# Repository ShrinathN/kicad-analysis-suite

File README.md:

# kicad-analysis-suite

**PCB Analysis Suite for KiCad**: a KiCad 10 plugin, also usable standalone, for analysing printed circuit boards. It has five tools so far:

- **DC & Thermal**: current density, IR drop and temperature on a real board, including resistance elements, linear and switching regulators (with their losses and junction temperature), current pulses (fusing) and magnetic field maps.
- **Switching Loop**: the hot loop and gate loops of a switching power stage (buck, boost, half-bridge, 4-switch buck-boost; synchronous or with a diode): loop inductance and where it sits, ringing frequency, gate-loop and common-source inductance, from a partial-inductance (PEEC) solve of the layout; switching edges in time, a snubber designer and an EMI estimate.
- **PDN (AC)**: the impedance of a supply rail seen by each chip, from the board's copper, the decoupling capacitors and the regulator, against the target impedance; which capacitors matter, plane resonances, and the rail's voltage over time when the loads step, with the regulator's control loop fitted to its datasheet's load-transient plot.
- **Trace R/L/C → SPICE**: R, L, C, Z₀ and delay of the copper between any pads, from a 2D field solve of each cross-section, exported as a SPICE RLC subcircuit.
- **Matching & Tolerance**: draw an RF matching network with real parts, then see whether it still meets its specs across part tolerances.

**Simulation tests**: keep any tool's setup as a test with pass / fail checks (T_max < 85 °C, the rail within its target, loop L < 3 nH, …) and rerun them whenever the board changes, from the command line, a Makefile or a script. Each run writes a report to `simulations/<timestamp>/` and compares it with the previous run:

```sh
python3 -m pcb_current_sim init board.kicad_pcb                       # tests from the setups you made in the windows
python3 -m pcb_current_sim run board.simtests.toml --test "3V3 rail"   # or --all; exit code 1 when a check fails
```

More tools (3D extraction, full-wave export, signal integrity) are planned. See the [roadmap](docs/ROADMAP.md).

## DC & Thermal

Pick the pads where current enters and leaves, or add voltage sources and loads, and solve all of them together on the board's copper.

| Current density | Temperature (electro-thermal) |
|---|---|
|  |  |
| **Magnetic field above the board** | **3D view** |
|  |  |

- Reads tracks, arcs, vias, filled zones, pads and the stackup directly from the `.kicad_pcb` file.
- Current paths, loads and voltage sources. Resistors on the board are found automatically, and any two pads can be joined by a resistance (FET R_on, inductor DCR, external load).
- Electro-thermal coupling with temperature-dependent copper resistance and natural convection plus radiation.
- Pulse heating and fusing, magnetic field maps and loop inductance.
- Tables per pad, via, track and element; export to PDF, HTML, CSV, PNG/SVG and ParaView.

## Switching Loop

Pick the switch node (or let the tool find it): it finds the switching parts, the hot-loop capacitors and the gate drives (driver pin, gate resistor, gate, return pin) and meshes the copper of all their nets, ground included, as conductors. A partial-inductance (PEEC) solve gives the copper's impedance between the parts' pins; the parts add their datasheet models (package inductance, capacitances, ESL).

- For each switching edge: the loop inductance across the switch that turns off, split into board copper and parts, and a bar chart of where it sits (each net and layer, vias, each package, each capacitor's ESL).
- The ringing frequency and Q with the switch's own capacitance, the expected overshoot per A/ns, and a starting snubber.
- Per FET: the gate-loop inductance, gate ringing, and the common-source inductance (the mutual between the gate loop and the power loop), which slows switching.
- Current-density and inductance-density maps at the ringing frequency, board capacitance between the nets, and a SPICE subcircuit of the copper (coupled inductors).

- **Switching edges** (simulated in time): one turn-on and one turn-off of the hard-switched switch at the inductor current you give, with the copper and the parts as one circuit: switch-node overshoot and ringing, dv/dt, di/dt, switching loss (E_on + E_off) × f_sw, reverse recovery, and how far the other FET's gate is pushed toward its threshold (shoot-through risk). A built-in solver uses the datasheet values; a FET can instead use its manufacturer's SPICE model, simulated in ngspice (bundled with KiCad).
- A cell diagram, readiness checks with one-click fixes, and a plain-language "What it means" summary.

| | |
|---|---|
|  |  |
|  |  |

## PDN (AC)

Pick a rail and its return nets: the tool finds the decoupling capacitors, the regulator and the chips on the rail, meshes the rail's copper over its return planes, and sweeps the impedance at every chip from 10 Hz to the GHz range.

- Z(f) at each load against Z_target = V × deviation / ΔI, for the bare board, with the capacitors, and complete; the anti-resonance peaks and plane resonances.
- A decap table: C at the rail voltage (DC bias), ESR, ESL, mounting inductance, resonance, distance to the nearest load and the band where each one carries the most current; "what if" each capacitor were left off.
- Voltage maps of the rail at a chosen frequency (where a plane resonance sits).
- The regulator as R + L or as its control loop, fitted to the load-transient plot of its datasheet: a built-in digitiser reads a screenshot (traces by colour, or by clicked points for black-and-white plots), and the fit transfers to your board's capacitance.
- Load steps: each chip's current as a SPICE-style PULSE, and the rail's voltage at each chip over time, split by which load causes it.
- Layout findings with their place on the board: voids and slots in the return plane the rail's current crosses, copper with no return under it, decaps with long return paths, chips with no decap nearby.
- Touchstone export (`.sNp`) of the complete rail between the loads, or of the bare board with a port at every load, decap and the regulator; regulator fits saved by part number for other boards.

| | |
|---|---|
|  |  |
|  |  |

## Trace R/L/C → SPICE

Pick two or more pads on one net and the return nets. The tool follows the copper between the pads (tracks, arcs, vias, stubs), solves the field of every cross-section against the return copper, and builds an RLC ladder.

- Any geometry: microstrip, stripline, coplanar lines, and a GND pour on the other side of a 2-layer board, all from one 2D field solver (within 2 % of Hammerstad–Jensen and Wheeler).
- DC R from the board's real copper (the DC solver), L and C per segment, via L and C, pad C, open stubs.
- Copper pours as real conductors: meshed over their return plane and reduced exactly to R, L and C between everything that touches them.
- Resistors, diodes, capacitors and inductors between any two pads, also across nets (trace → part → trace), with return-net pads as the reference.
- Outputs: per-path totals, a segment table with Z₀ and the return found, the path coloured by Z₀ with impedance steps marked, a drawn schematic of the ladder, and a `.subckt` of plain R, L and C that runs in any SPICE.

The example below is a DC-DC converter's input path on a 2-layer board: from the input connector through a supply pour, the inductor (added as an element) and the switch-node pour to the switch, over a ground plane. The input capacitors are capacitor elements to ground.

| | |
|---|---|
|  |  |
|  |  |

## Matching & Tolerance

Build a ladder network in a visual editor: the symbols appear as you add parts, and the plots follow every edit.

| Monte Carlo S11 against the spec | Yield histograms |
|---|---|
|  |  |
| **Smith chart** | **Sensitivity** |
|  |  |

- Series and shunt L, C and R, transmission lines (ideal, or microstrip from the board stackup), open and shorted stubs, and S2P two-ports.
- Real parts from a shared component library: tolerance, Q, self-resonance, ESR, ESL, and capacitor drift with temperature and DC bias.
- Source and load as R + jX, an RLC model or a measured `.s1p` file.
- Corners, Monte Carlo (uniform or Gaussian), a worst-case search, sensitivity, yield per band and a BOM.

The screenshot example matches a small 2.4 GHz antenna (20 Ω + 1.5 nH + 3 pF) to 50 Ω. It uses a 1.3 pF shunt capacitor and a 1.5 nH series inductor, both 0402 parts with ±0.1 pF / ±0.1 nH tolerance.

## Shared panels

| Stackup & materials | Component library |
|---|---|
|  |  |

## Install

1. Install KiCad 10 and enable the API: *Preferences → Plugins → Enable KiCad API*.
2. Either install the zip package: run `python3 kicad_plugin/build_pcm.py` (writes `dist/kicad-analysis-suite-<version>.zip`), then in KiCad open *Plugin and Content Manager → Install from File…* and pick the zip.
   Or run `kicad_plugin/install.sh`, which copies the plugin into the plugin folder of a native or Flatpak KiCad. Use one method, not both.
3. Restart the PCB editor. On first load KiCad installs the Python dependencies (numpy, scipy, matplotlib, plotly, kicad-python), which needs network access.
4. Two toolbar buttons appear: **PCB Analysis Suite** opens the Home window, and **DC & Thermal** opens that tool directly.

Save the board (and refill zones) before running: the tools read the saved `.kicad_pcb` file.

Standalone, without KiCad running:

```sh
python3 -m pcb_current_sim.wxgui board.kicad_pcb --home                        # wx GUI, Home window
python3 -m pcb_current_sim board.kicad_pcb --row "J1.2>J2.2:3" --out results   # command line
```

## Documentation

- [Documentation (HTML)](docs/index.html): what each tool does, how it works, its limits, interactive calculators and realistic use cases for every tool. Open the file in any browser; it needs no network.
- [User guide](docs/USER_GUIDE.md): every tool and option, the physical models, outputs and the CLI.
- [Development](docs/DEVELOPMENT.md): environment, tests, smoke tests, screenshots and code layout.
- [Roadmap](docs/ROADMAP.md): the plan for the remaining tools.
- [CLAUDE.md](CLAUDE.md): the detailed design log kept during development.

## Status

- DC & Thermal, Switching Loop (inductance, ringing, switching transients), Trace R/L/C → SPICE and Matching & Tolerance work and are covered by tests (`python3 -m pytest tests`).
- Tested in a running KiCad 10 (Flatpak): both toolbar buttons and the KiCad link (pad selection, save, refill).
- Developed and tested on Linux with the KiCad 10 Flatpak.

## License

[GPL-3.0](LICENSE), the same licence as KiCad. You may use, modify and share this software. If you distribute it, or a modified version, you must do so under the same licence and include the source.

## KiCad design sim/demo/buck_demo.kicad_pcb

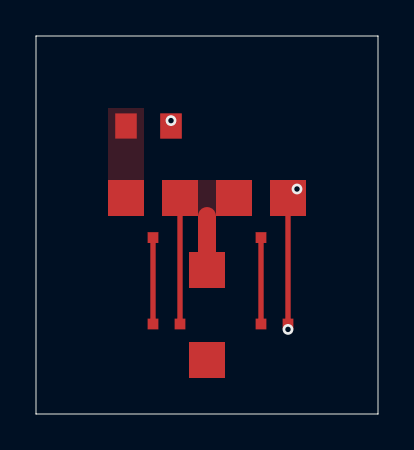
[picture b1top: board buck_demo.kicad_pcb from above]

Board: 2 copper layers, 19.0 x 21.0 mm, 5 parts (0 on the bottom side), 5 nets.

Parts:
C1: 10u; t
L1: 4u7; t
Q1, Q2: x; t
U1: driver; t

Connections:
G1: Q1.3, U1.1
G2: Q2.3, U1.3
GND: C1.2, Q2.2, U1.4
SW: L1.1, Q1.2, Q2.1, U1.2
VIN: C1.1, Q1.1

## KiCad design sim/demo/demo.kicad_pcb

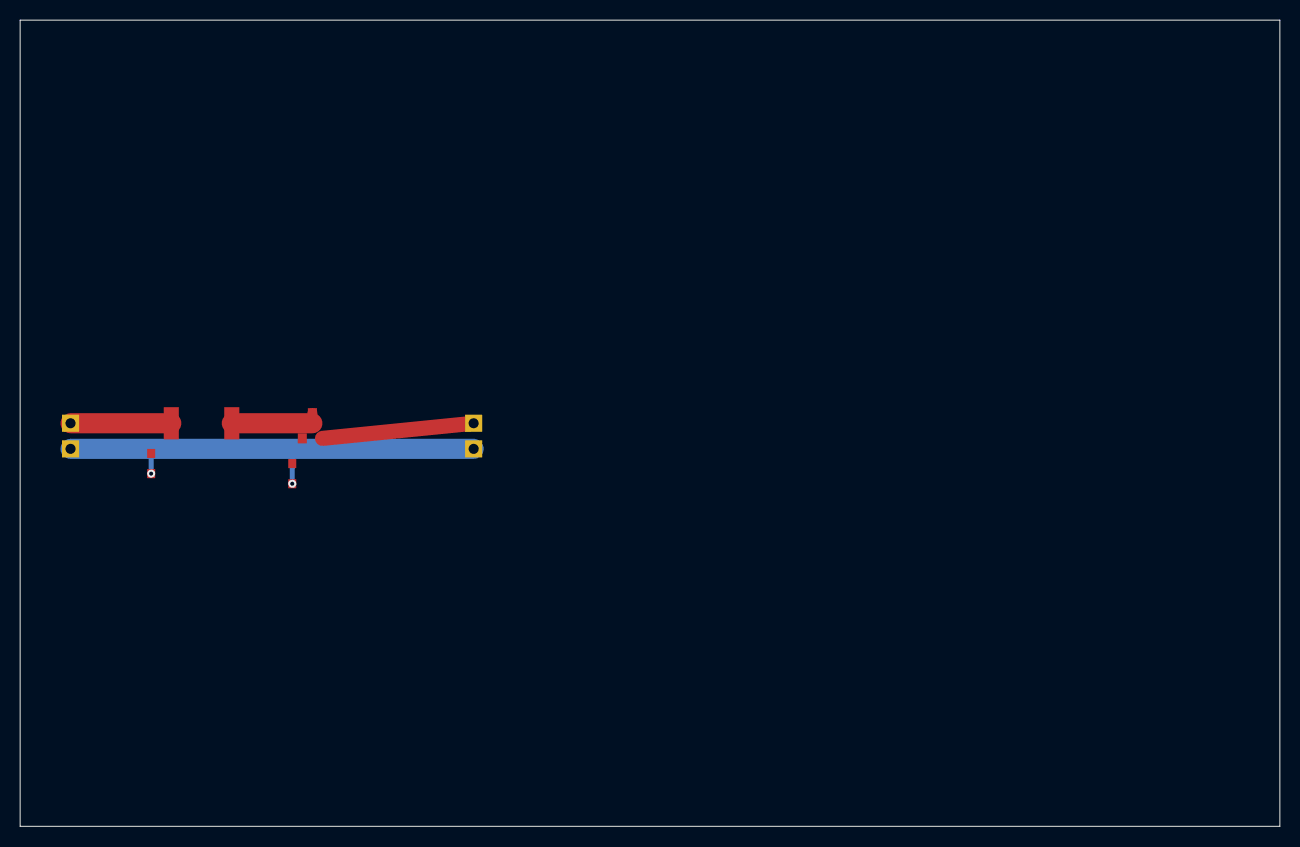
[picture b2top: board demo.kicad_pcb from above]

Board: 2 copper layers, 125.0 x 80.0 mm, 6 parts (0 on the bottom side), 5 nets.

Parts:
J1, J2: Conn; Conn_1x02
Q1: AO3400; SOT-23
R1: 5m; R_2512_6332Metric
R2: 10k; R_0603_1608Metric
R3: 100k; R_0603_1608Metric

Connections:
GATE: Q1.1, R2.1
GND: J1.2, J2.2, R2.2, R3.2
LOAD: J2.1, Q1.2
SNS: Q1.3, R1.2
VIN: J1.1, R1.1, R3.1
